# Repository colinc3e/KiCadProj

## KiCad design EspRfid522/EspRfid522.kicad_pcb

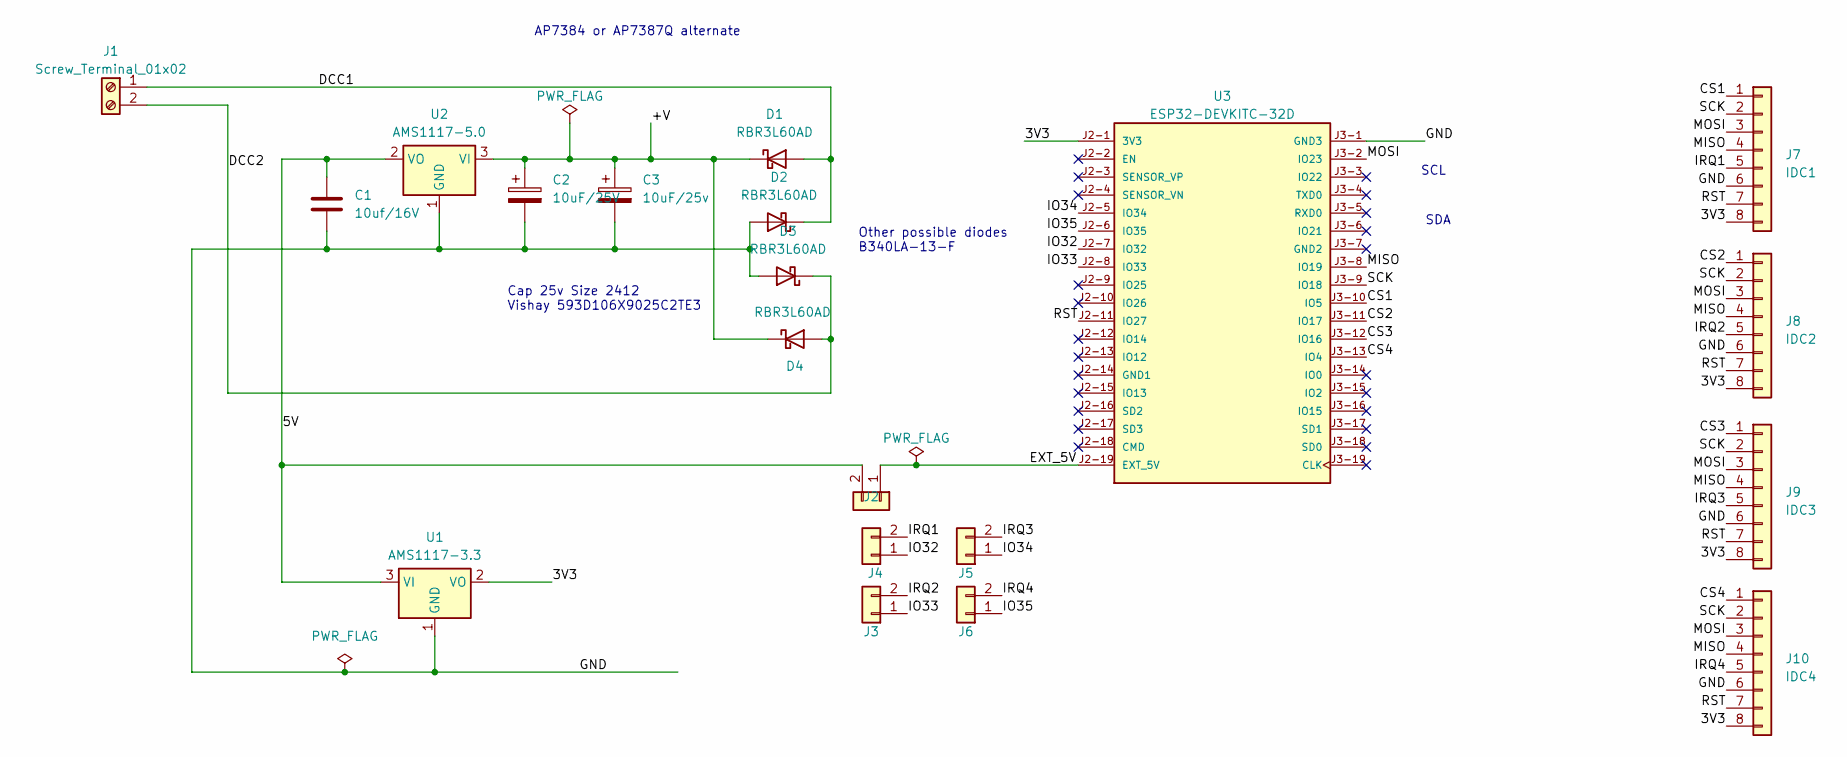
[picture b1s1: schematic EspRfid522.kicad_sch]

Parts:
C1: 10uf/16V; C_1206_3216Metric_Pad1.33x1.80mm_HandSolder
C2: 10uF/25V; CP_EIA-6032-20_AVX-F_Pad2.25x2.35mm_HandSolder
C3: 10uF/25v; CP_EIA-6032-20_AVX-F_Pad2.25x2.35mm_HandSolder
D1, D2, D3, D4: RBR3L60AD; D_SMA_Handsoldering
J1: Screw_Terminal_01x02; TerminalBlock_Phoenix_PT-1,5-2-3.5-H_1x02_P3.50mm_Horizontal
J2, J3, J4, J5, J6: Conn_01x02; PinHeader_1x02_P2.54mm_Vertical
J7: IDC1; IDC-Header_2x04_P2.54mm_Vertical
J8: IDC2; IDC-Header_2x04_P2.54mm_Vertical
J9: IDC3; IDC-Header_2x04_P2.54mm_Vertical
J10: IDC4; IDC-Header_2x04_P2.54mm_Vertical
U1: AMS1117-3.3; SOT-223-3_TabPin2
U2: AMS1117-5.0; SOT-223-3_TabPin2
U3: ESP32-DEVKITC-32D; MODULE_ESP32-DEVKITC-32D; PARTREV V4

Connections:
/3V3: J7.8, J8.8, J9.8, J10.8, U1.2 (VO), U3.J2-1 (3V3)
/5V: C1.1, J4.2, U1.3 (VI), U2.2 (VO)
/+V: C2.1, C3.1, D1.1 (K), D4.1 (K), U2.3 (VI)
/CS1: J7.1, U3.J3-10 (IO5)
/CS2: J8.1, U3.J3-11 (IO17)
/CS3: J9.1, U3.J3-12 (IO16)
/CS4: J10.1, U3.J3-13 (IO4)
/DCC1: D1.2 (A), D2.1 (K), J1.1
/DCC2: D3.1 (K), D4.2 (A), J1.2
/EXT_5V: J4.1, U3.J2-19 (EXT_5V)
/GND: C1.2, C2.2, C3.2, D2.2 (A), D3.2 (A), J7.6, J8.6, J9.6, J10.6, U1.1 (GND), U2.1 (GND), U3.J3-1 (GND3)
/IO32: J2.1, U3.J2-7 (IO32)
/IO33: J3.1, U3.J2-8 (IO33)
/IO34: J5.1, U3.J2-5 (IO34)
/IO35: J6.1, U3.J2-6 (IO35)
/IRQ1: J2.2, J7.5
/IRQ2: J3.2, J8.5
/IRQ3: J5.2, J9.5
/IRQ4: J6.2, J10.5
/MISO: J7.4, J8.4, J9.4, J10.4, U3.J3-8 (IO19)
/MOSI: J7.3, J8.3, J9.3, J10.3, U3.J3-2 (IO23)
/RST: J7.7, J8.7, J9.7, J10.7, U3.J2-11 (IO27)
/SCK: J7.2, J8.2, J9.2, J10.2, U3.J3-9 (IO18)

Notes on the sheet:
SDA
AP7384 or AP7387Q alternate
Other possible diodes B340LA-13-F
SCL
Cap 25v Size 2412 Vishay 593D106X9025C2TE3

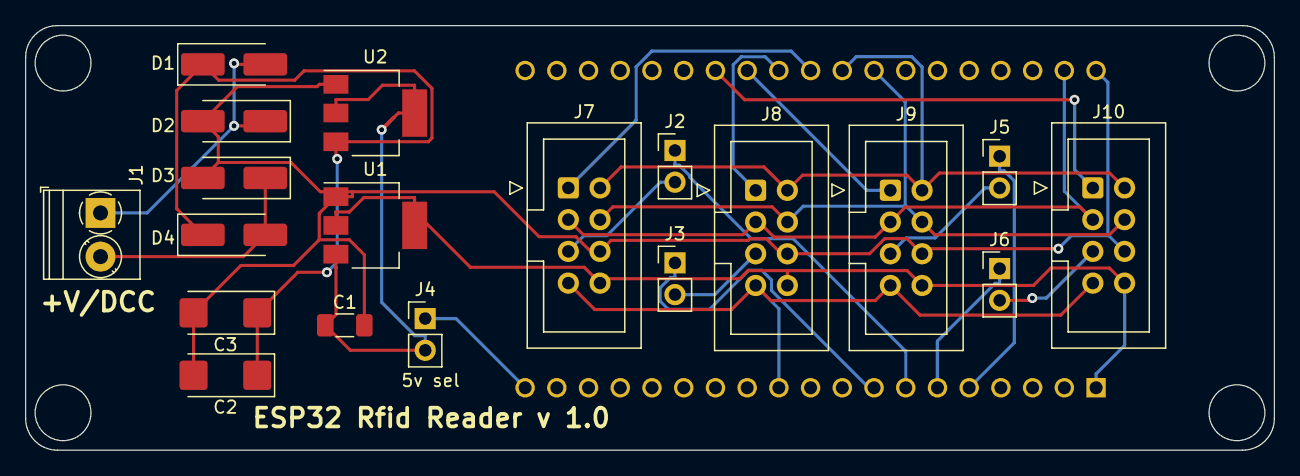
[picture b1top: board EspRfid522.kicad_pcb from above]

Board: 2 copper layers, 100.0 x 34.0 mm, 20 parts (1 on the bottom side), 23 nets.

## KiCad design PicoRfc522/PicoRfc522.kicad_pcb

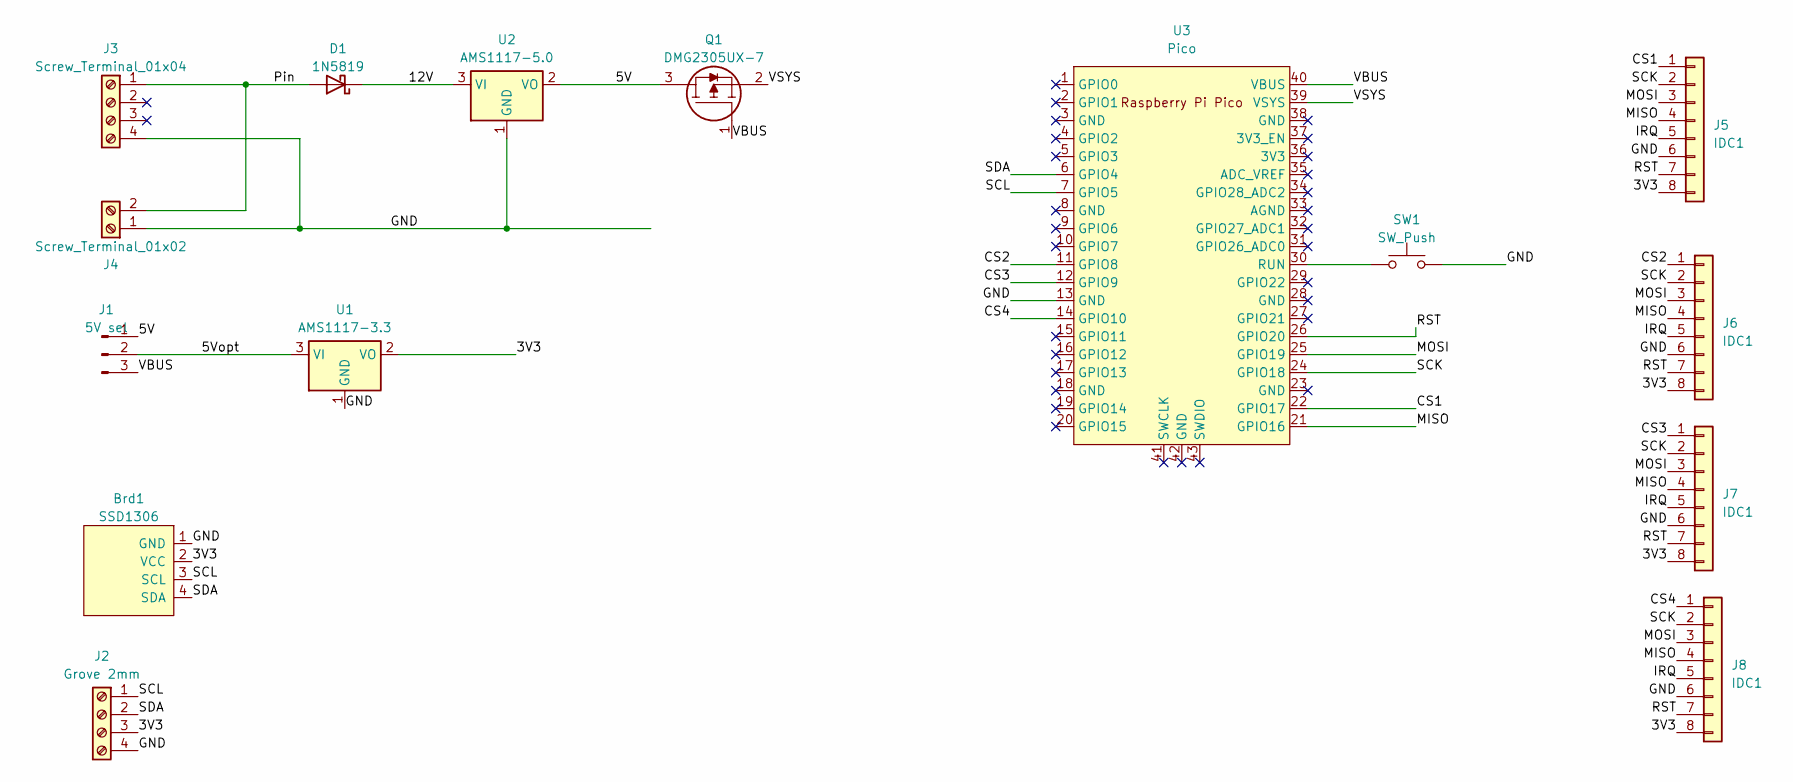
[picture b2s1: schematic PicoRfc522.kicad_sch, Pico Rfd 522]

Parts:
Brd1: SSD1306; 128x64OLED
D1: 1N5819; D_DO-41_SOD81_P10.16mm_Horizontal
J1: 5V sel; PinHeader_1x03_P2.54mm_Vertical
J2: Grove 2mm; HW4-2.0
J3: Screw_Terminal_01x04; TerminalBlock_Phoenix_PT-1,5-4-3.5-H_1x04_P3.50mm_Horizontal
J4: Screw_Terminal_01x02; TerminalBlock_Phoenix_PT-1,5-2-3.5-H_1x02_P3.50mm_Horizontal
J5, J6, J7, J8: IDC1; IDC-Header_2x04_P2.54mm_Vertical
Q1: DMG2305UX-7; SOT96P240X110-3N; Mouser Part Number 621-DMG2305UX-7
SW1: SW_Push; SW_Tactile_SPST_NO_Straight_CK_PTS636Sx25SMTRLFS
U1: AMS1117-3.3; SOT-223-3_TabPin2
U2: AMS1117-5.0; SOT-223-3_TabPin2
U3: Pico; RPi_Pico_SMD_TH

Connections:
/3V3: Brd1.2 (VCC), J2.3, J5.8, J6.8, J7.8, J8.8, U1.2 (VO)
/5V: J1.1, Q1.3, U2.2 (VO)
/5Vopt: J1.2, U1.3 (VI)
/12V: D1.1 (K), U2.3 (VI)
/CS1: J5.1, U3.22 (GPIO17)
/CS2: J6.1, U3.11 (GPIO8)
/CS3: J7.1, U3.12 (GPIO9)
/CS4: J8.1, U3.14 (GPIO10)
/GND: Brd1.1 (GND), J2.4, J3.4, J4.1, J5.6, J6.6, J7.6, J8.6, SW1.1, U1.1 (GND), U2.1 (GND), U3.13 (GND)
/IRQ: J5.5, J6.5, J7.5, J8.5
/MISO: J5.4, J6.4, J7.4, J8.4, U3.21 (GPIO16)
/MOSI: J5.3, J6.3, J7.3, J8.3, U3.25 (GPIO19)
/Pin: D1.2 (A), J3.1, J4.2
/RST: J5.7, J6.7, J7.7, J8.7, U3.26 (GPIO20)
/SCK: J5.2, J6.2, J7.2, J8.2, U3.24 (GPIO18)
/SCL: Brd1.3 (SCL), J2.1, U3.7 (GPIO5)
/SDA: Brd1.4 (SDA), J2.2, U3.6 (GPIO4)
/VBUS: J1.3, Q1.1, U3.40 (VBUS)
/VSYS: Q1.2, U3.39 (VSYS)
unnamed: SW1.2, U3.30 (RUN)

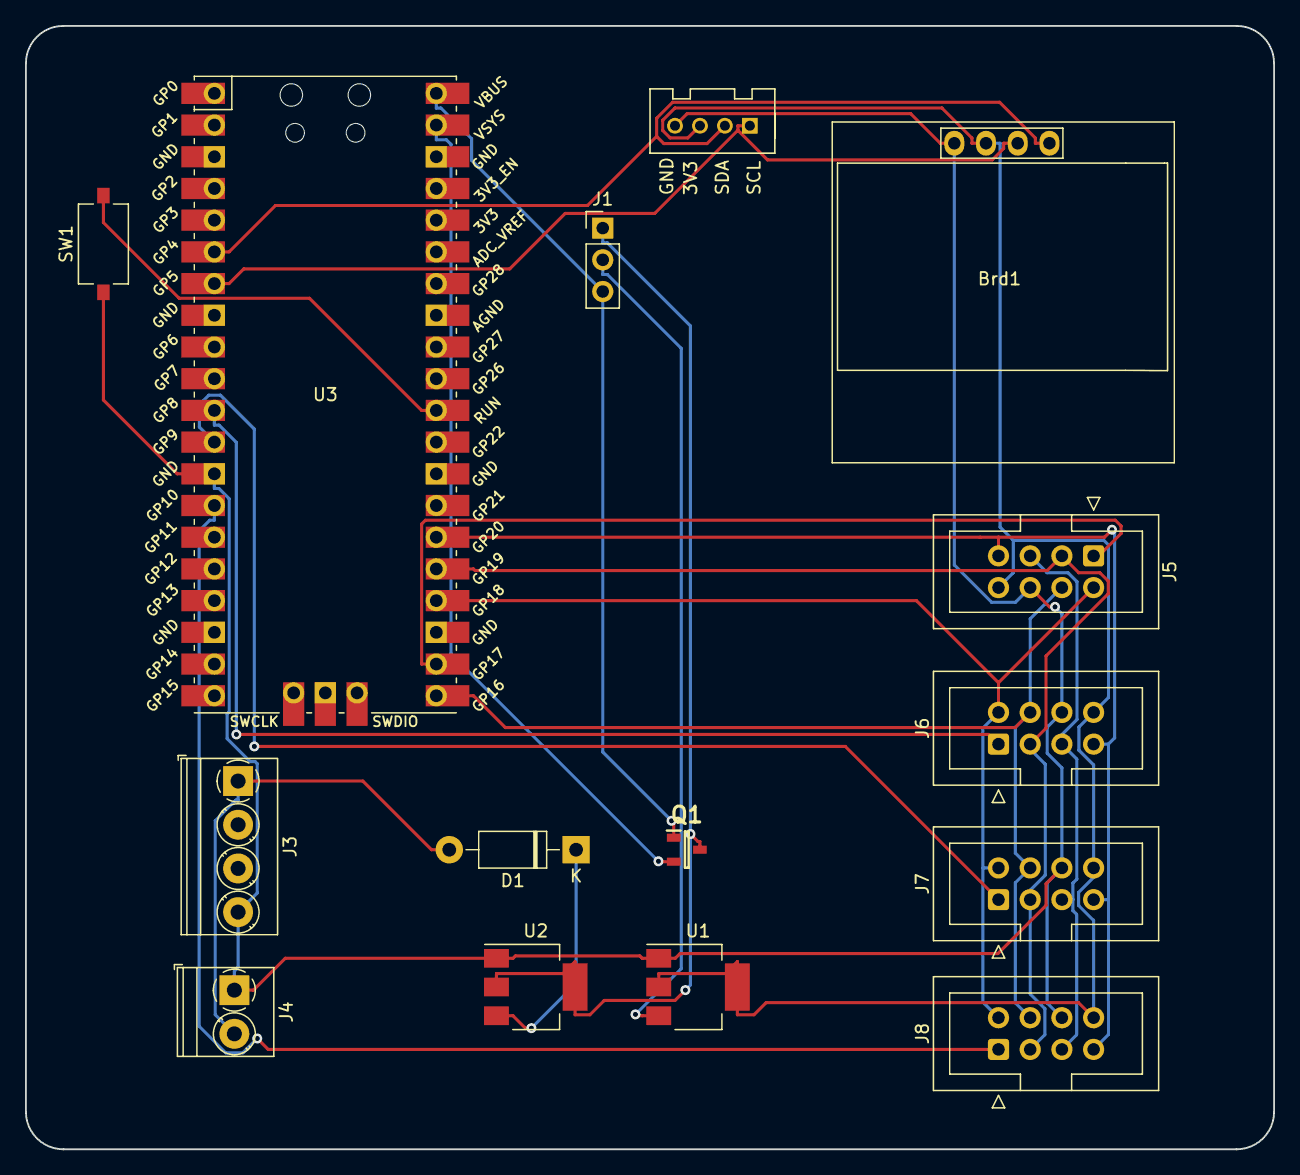
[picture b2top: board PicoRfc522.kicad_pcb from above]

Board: 2 copper layers, 100.0 x 90.0 mm, 15 parts (0 on the bottom side), 20 nets.

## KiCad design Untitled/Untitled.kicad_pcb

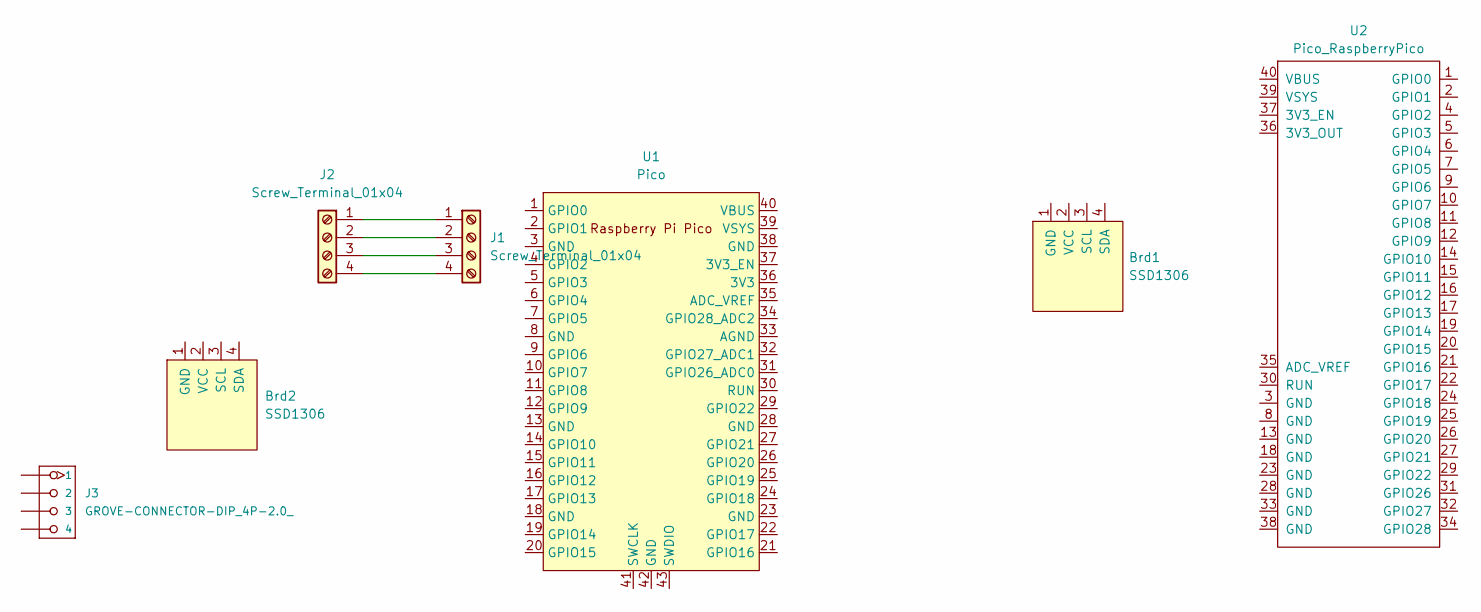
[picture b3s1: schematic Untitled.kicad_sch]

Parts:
Brd1, Brd2: SSD1306; 128x64OLED
J1, J2: Screw_Terminal_01x04; TerminalBlock_Phoenix_PT-1,5-4-3.5-H_1x04_P3.50mm_Horizontal
J3: GROVE-CONNECTOR-DIP_4P-2.0_; HW4-2.0
U1: Pico; RPi_Pico_SMD_TH
U2: Pico_RaspberryPico; RPi_Pico_SMD_TH

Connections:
unnamed: J1.1, J2.1
unnamed: J1.2, J2.2
unnamed: J1.3, J2.3
unnamed: J1.4, J2.4

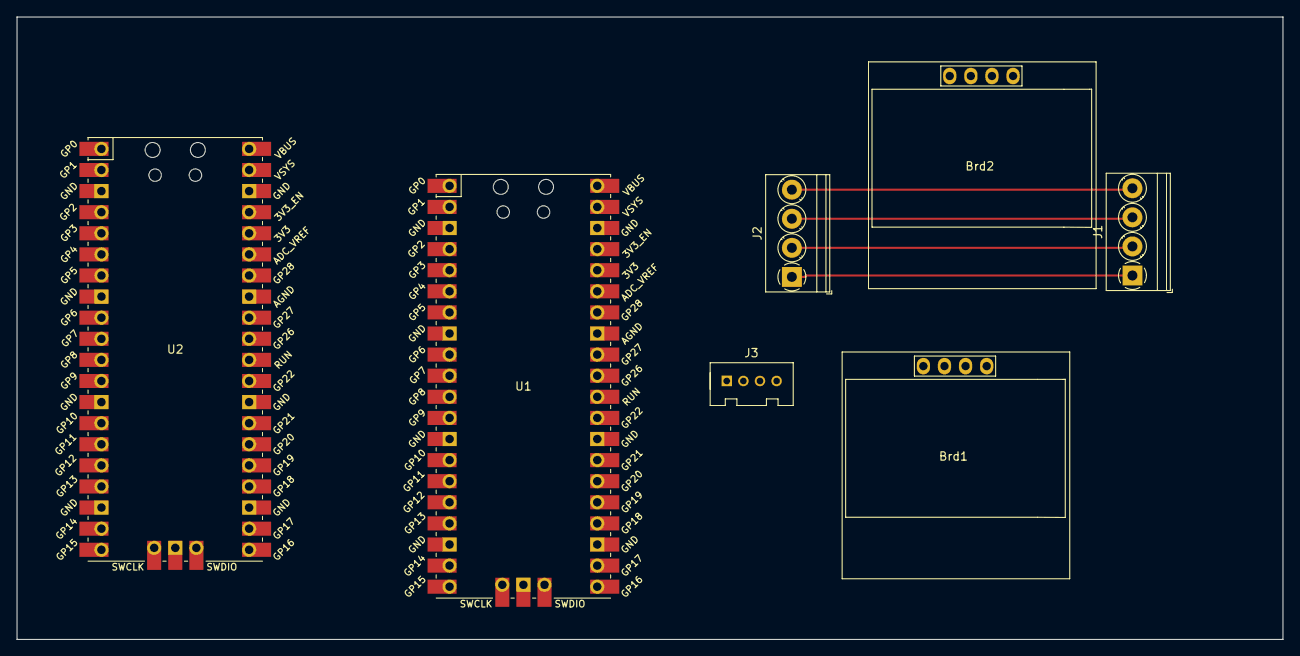
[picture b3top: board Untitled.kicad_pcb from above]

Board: 2 copper layers, 152.4 x 74.9 mm, 7 parts (0 on the bottom side), 4 nets.

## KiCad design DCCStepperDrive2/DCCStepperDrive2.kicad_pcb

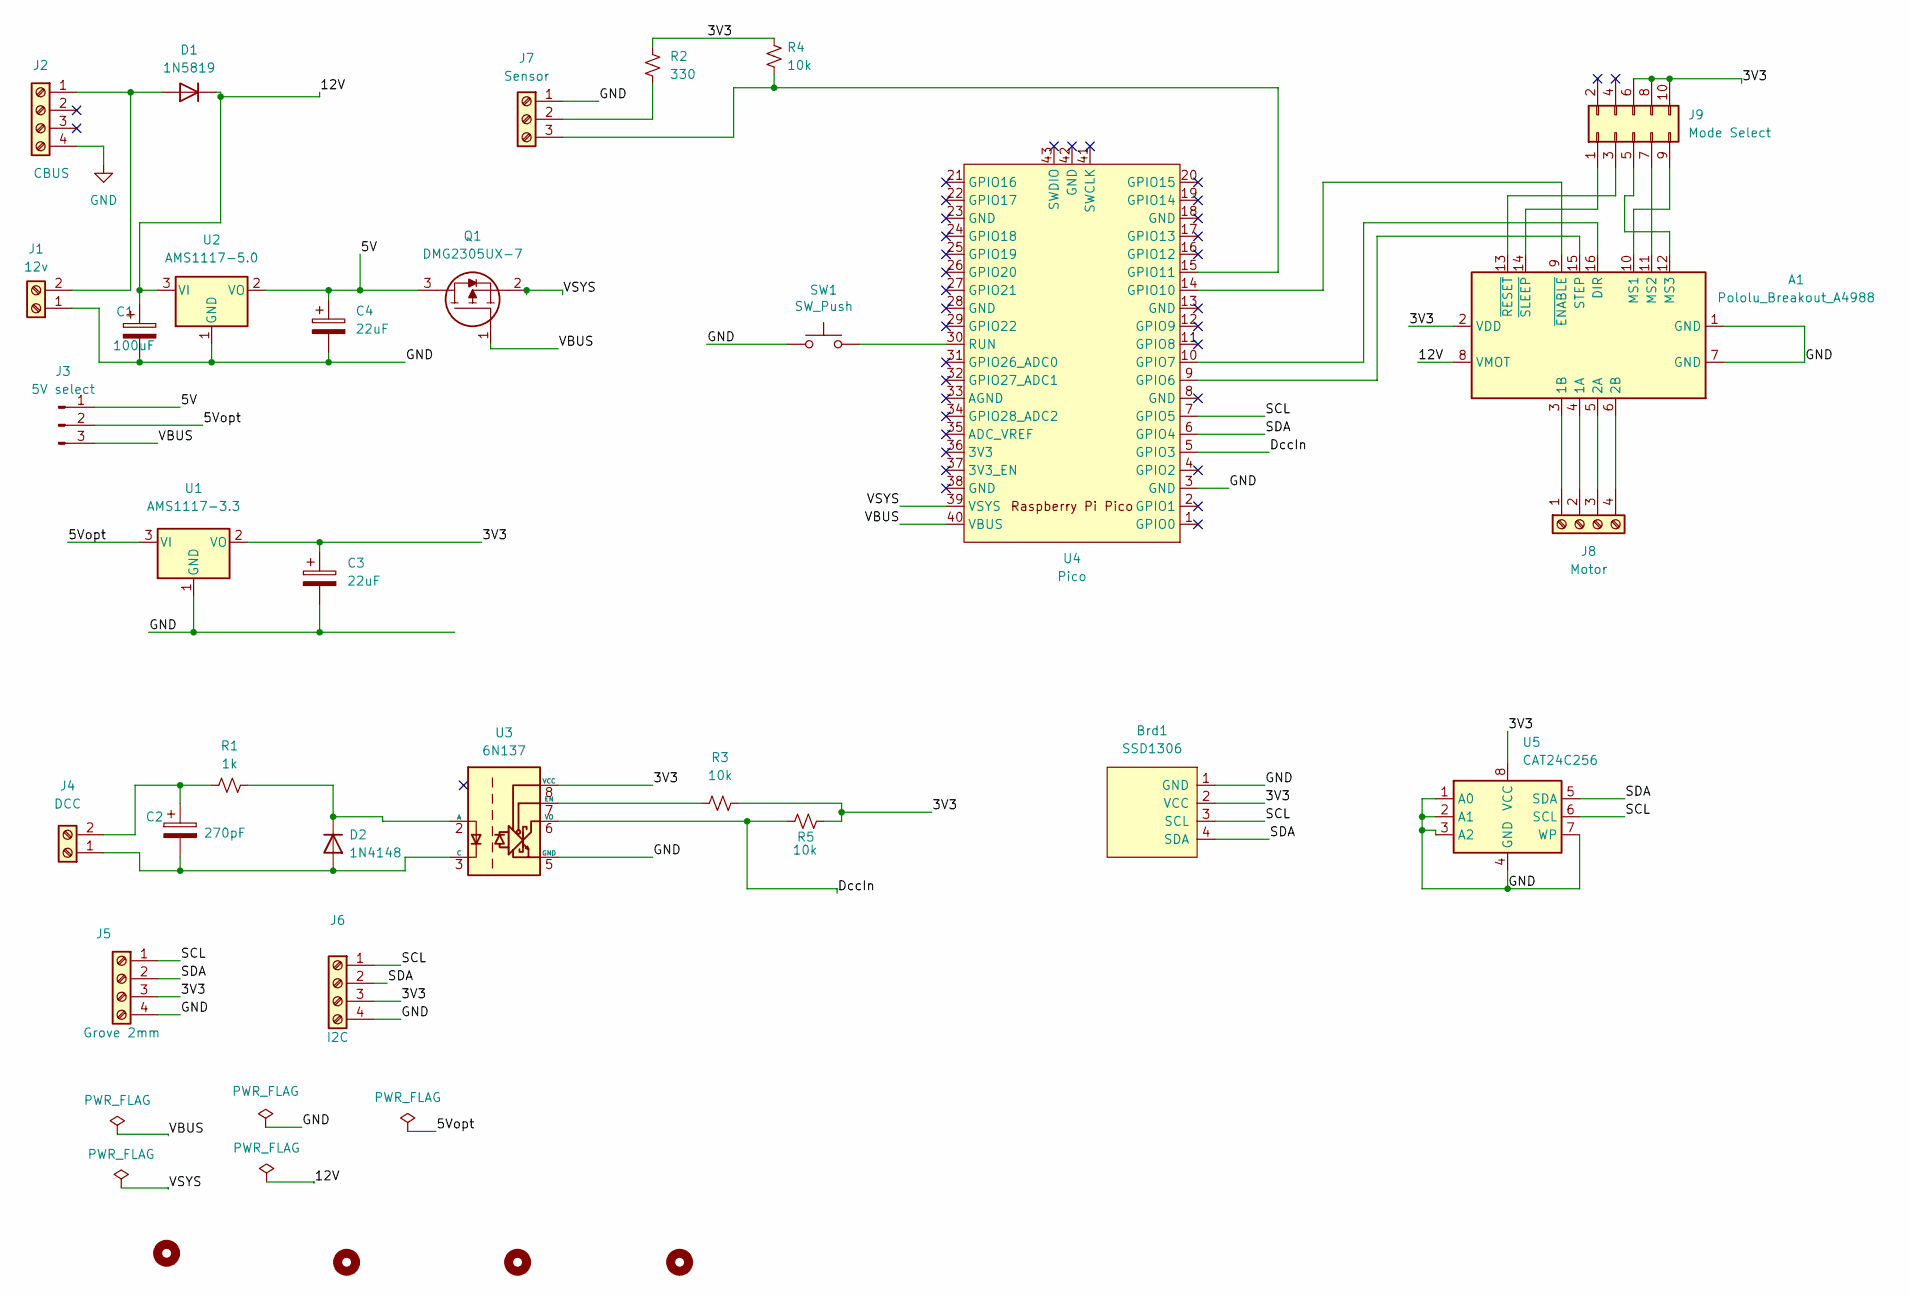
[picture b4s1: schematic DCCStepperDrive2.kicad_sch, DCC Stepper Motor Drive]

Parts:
A1: Pololu_Breakout_A4988; Pololu_Breakout-16_15.2x20.3mm
Brd1: SSD1306; 128x64OLED
C1: 100uF; CP_Radial_D10.0mm_P7.50mm
C2: 270pF; CP_Radial_Tantal_D7.0mm_P5.00mm
C3, C4: 22uF; CP_Radial_Tantal_D7.0mm_P5.00mm
D1: 1N5819; D_DO-41_SOD81_P10.16mm_Horizontal
D2: 1N4148; D_DO-35_SOD27_P7.62mm_Horizontal
H1, H2, H3, H4: MountingHole; MountingHole_3.2mm_M3
J1: 12v; TerminalBlock_Phoenix_PT-1,5-2-3.5-H_1x02_P3.50mm_Horizontal
J2: CBUS; TerminalBlock_Phoenix_PT-1,5-4-3.5-H_1x04_P3.50mm_Horizontal
J3: 5V select; PinHeader_1x03_P2.54mm_Vertical
J4: DCC; TerminalBlock_Phoenix_PT-1,5-2-3.5-H_1x02_P3.50mm_Horizontal
J5: Grove 2mm; HW4-2.0
J6: I2C; HW4-2.0
J7: Sensor; TerminalBlock_Phoenix_PT-1,5-3-3.5-H_1x03_P3.50mm_Horizontal
J8: Motor; TerminalBlock_Phoenix_PT-1,5-4-3.5-H_1x04_P3.50mm_Horizontal
J9: Mode Select; PinHeader_2x05_P2.54mm_Vertical
Q1: DMG2305UX-7; SOT-23-3; Mouser Part Number 621-DMG2305UX-7
R1: 1k; R_1206_3216Metric
R2: 330; R_1206_3216Metric
R3, R4, R5: 10k; R_1206_3216Metric
SW1: SW_Push; SW_Tactile_SPST_NO_Straight_CK_PTS636Sx25SMTRLFS
U1: AMS1117-3.3; SOT-223-3_TabPin2
U2: AMS1117-5.0; SOT-223-3_TabPin2
U3: 6N137; DIP-8_W7.62mm
U4: Pico; RPi_Pico_SMD_TH
U5: CAT24C256; DIP-8_W7.62mm_LongPads

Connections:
/3V3: A1.2 (VDD), Brd1.2 (VCC), C3.1, J5.3, J6.3, J9.6, J9.8, J9.10, R2.2, R3.2, R4.2, R5.2, U1.2 (VO), U3.8 (VCC), U5.8 (VCC)
/5V: C4.1, J3.1, Q1.3, U2.2 (VO)
/5Vopt: J3.2, U1.3 (VI)
/12V: A1.8 (VMOT), C1.1, D1.1 (K), U2.3 (VI)
/DccIn: R5.1, U3.6 (VO), U4.5 (GPIO3)
/SCL: Brd1.3 (SCL), J5.1, J6.1, U4.7 (GPIO5), U5.6 (SCL)
/SDA: Brd1.4 (SDA), J5.2, J6.2, U4.6 (GPIO4), U5.5 (SDA)
/VBUS: J3.3, Q1.1, U4.40 (VBUS)
/VSYS: Q1.2, U4.39 (VSYS)
GND: A1.1 (GND), A1.7 (GND), Brd1.1 (GND), C1.2, C3.2, C4.2, J1.1, J2.4, J5.4, J6.4, J7.1, SW1.1, U1.1 (GND), U2.1 (GND), U3.5 (GND), U4.3 (GND), U5.1 (A0), U5.2 (A1), U5.3 (A2), U5.4 (GND), U5.7 (WP)
unnamed: A1.4 (1A), J8.2
unnamed: A1.3 (1B), J8.1
unnamed: A1.5 (2A), J8.3
unnamed: A1.6 (2B), J8.4
unnamed: A1.16 (DIR), U4.10 (GPIO7)
unnamed: A1.10 (MS1), J9.9
unnamed: A1.11 (MS2), J9.7
unnamed: A1.12 (MS3), J9.5
unnamed: A1.15 (STEP), U4.9 (GPIO6)
unnamed: A1.9 (~ENABLE), U4.14 (GPIO10)
unnamed: A1.13 (~RESET), J9.3
unnamed: A1.14 (~SLEEP), J9.1
unnamed: D1.2 (A), J1.2, J2.1
unnamed: C2.2, D2.2 (A), J4.1, U3.3 (C)
unnamed: D2.1 (K), R1.2, U3.2 (A)
unnamed: C2.1, J4.2, R1.1
unnamed: J7.2, R2.1
unnamed: J7.3, R4.1, U4.15 (GPIO11)
unnamed: R3.1, U3.7 (EN)
unnamed: SW1.2, U4.30 (RUN)

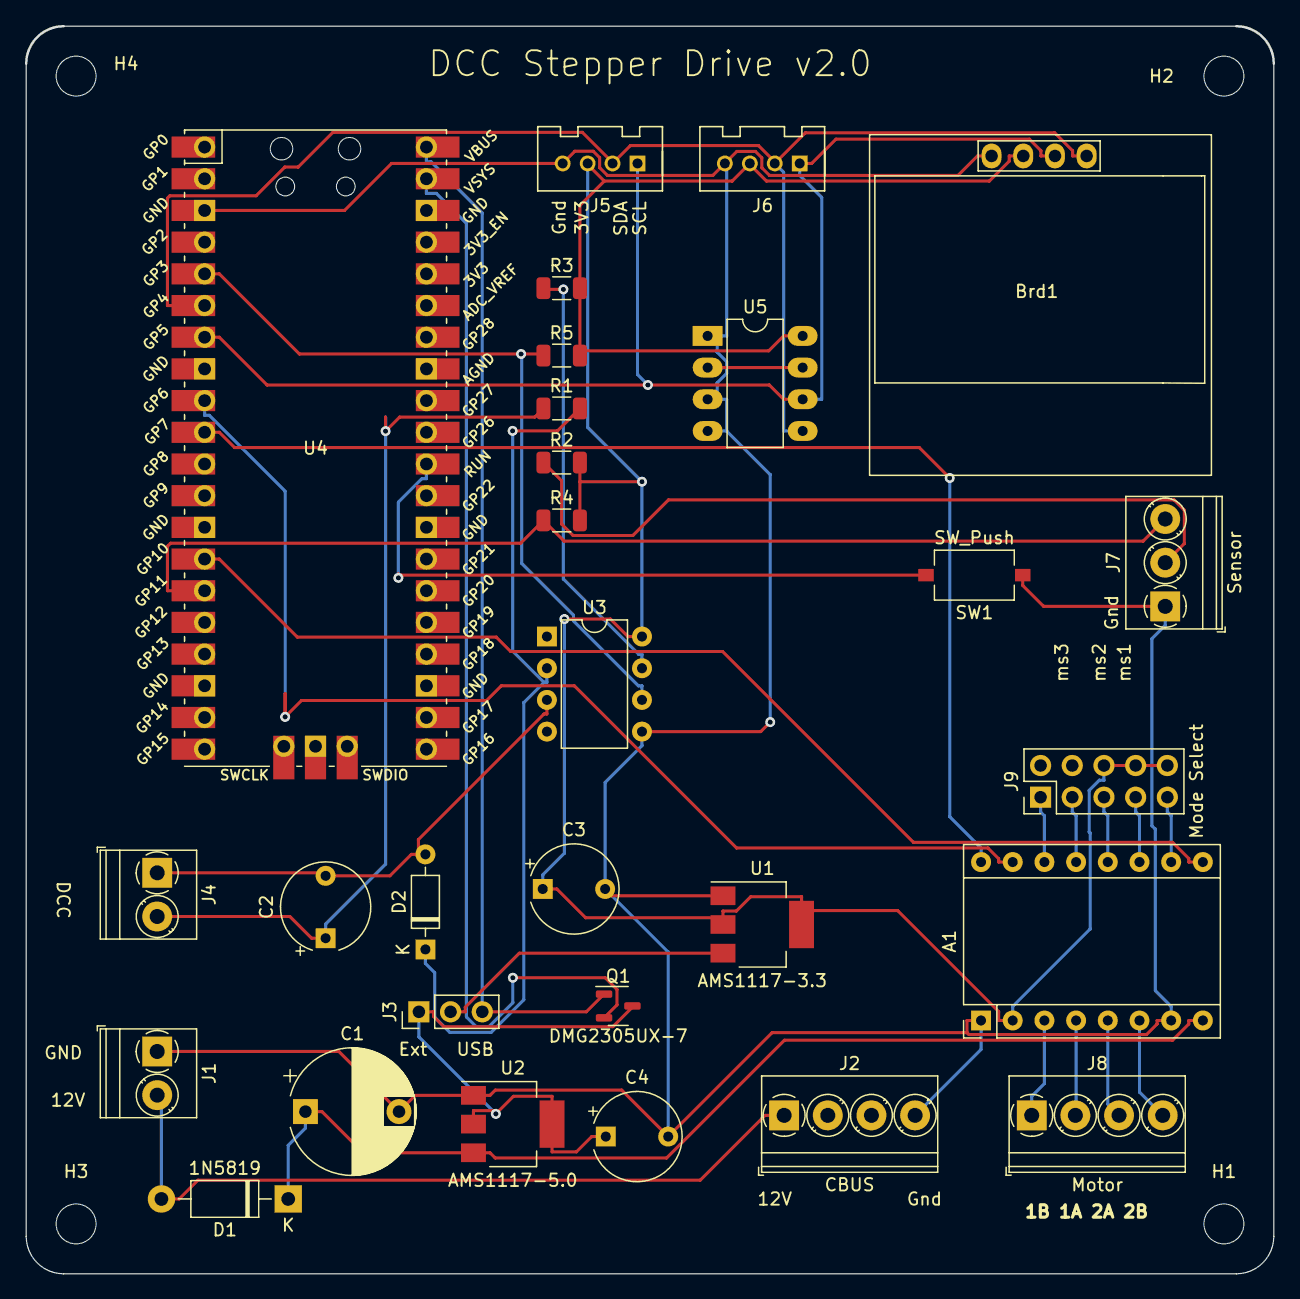
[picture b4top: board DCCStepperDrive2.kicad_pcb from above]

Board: 2 copper layers, 100.0 x 100.0 mm, 33 parts (0 on the bottom side), 30 nets.

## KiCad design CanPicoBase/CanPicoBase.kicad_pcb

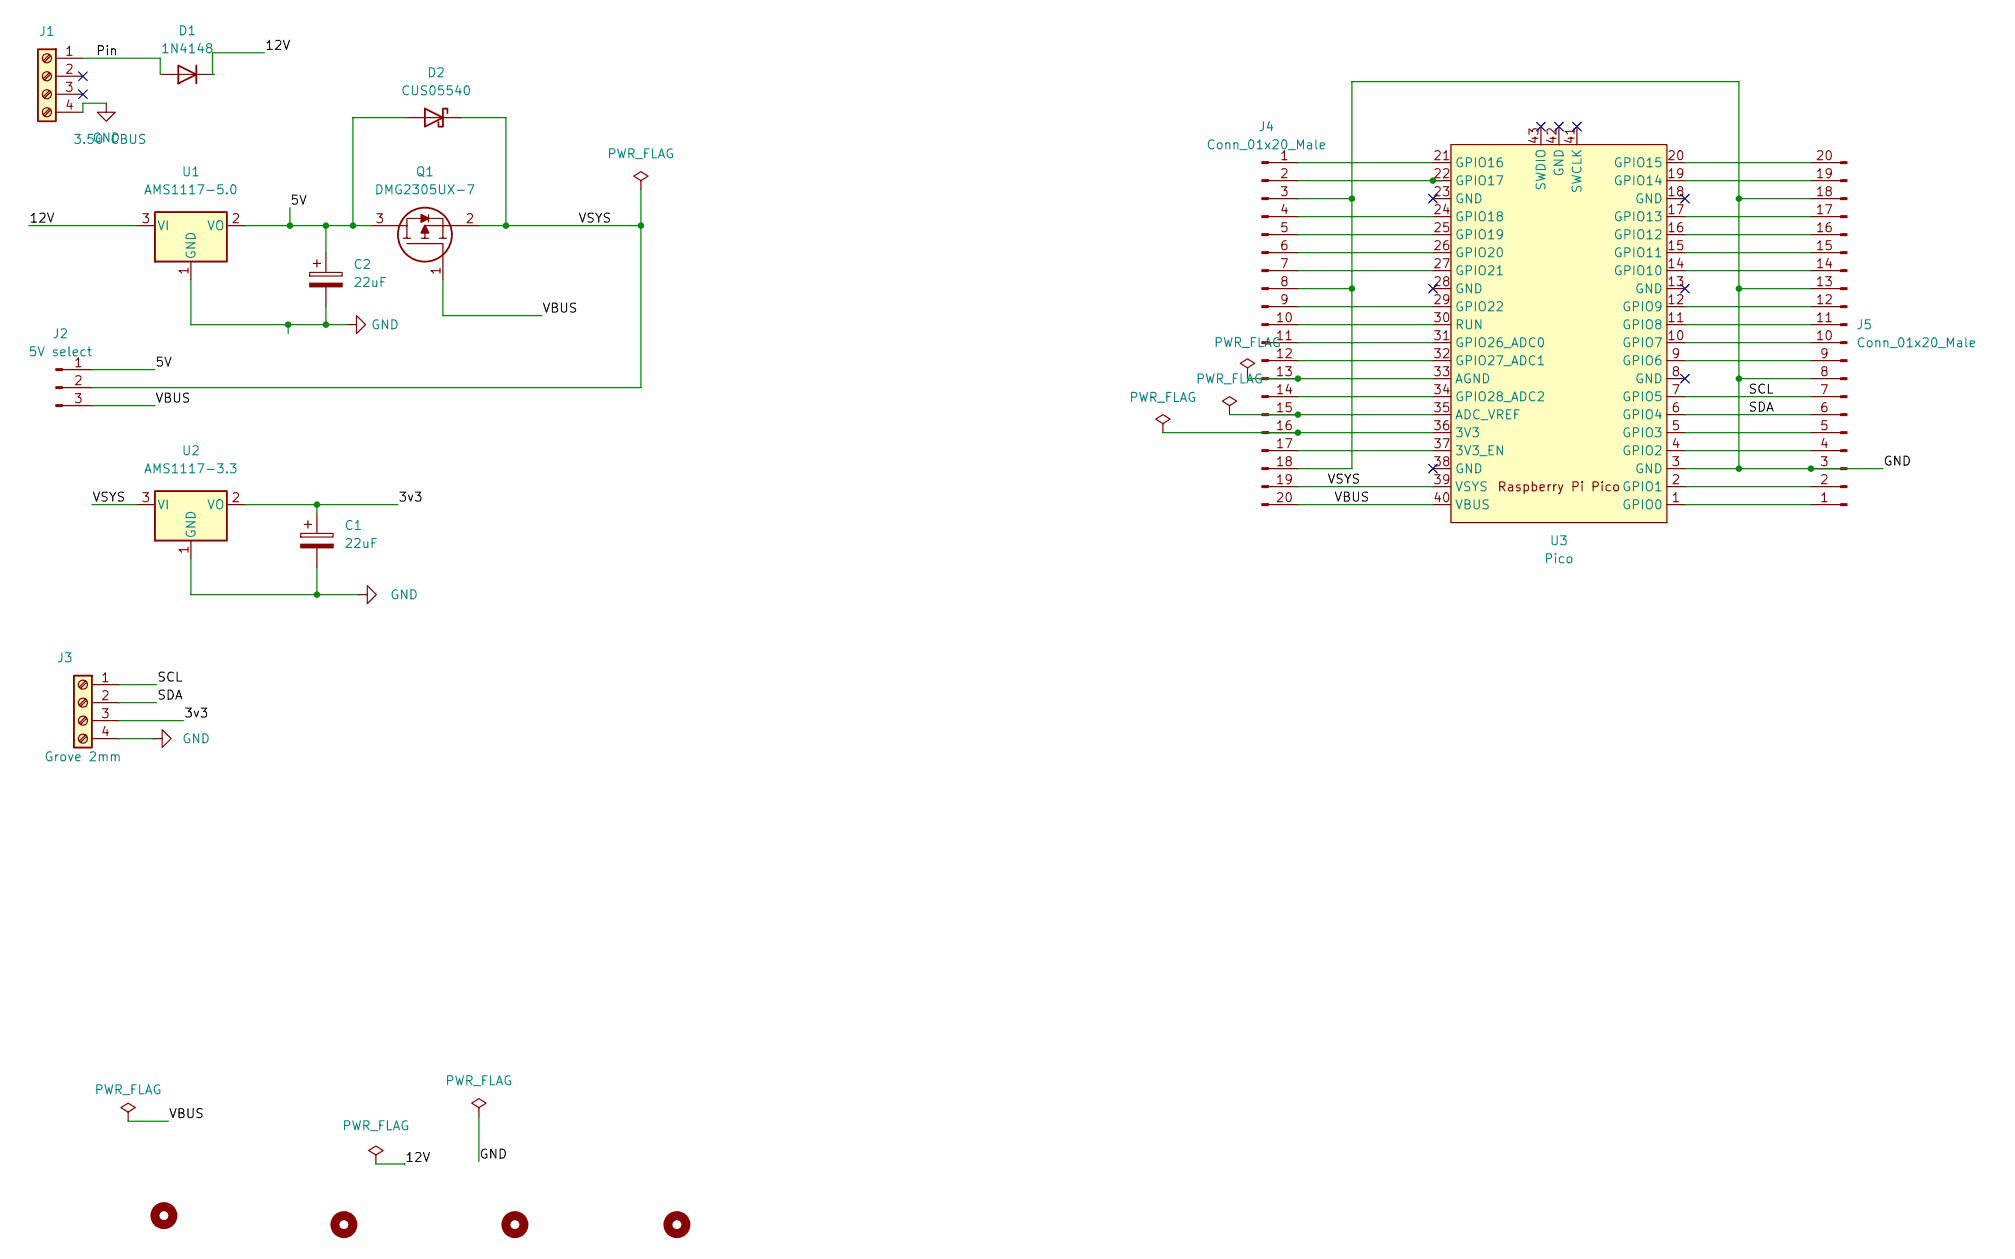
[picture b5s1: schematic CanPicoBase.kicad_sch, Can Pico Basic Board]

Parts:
C1, C2: 22uF; CP_Radial_Tantal_D7.0mm_P5.00mm
D1: 1N4148; D_DO-35_SOD27_P7.62mm_Horizontal
D2: CUS05540; D_SOD-123
H1, H2, H3, H4: MountingHole; MountingHole_3.2mm_M3
J1: 3.50 CBUS; TerminalBlock_Phoenix_PT-1,5-4-3.5-H_1x04_P3.50mm_Horizontal
J2: 5V select; PinHeader_1x03_P2.54mm_Vertical
J3: Grove 2mm; HW4-2.0
J4, J5: Conn_01x20_Male; PinSocket_1x20_P2.54mm_Vertical
Q1: DMG2305UX-7; SOT-23; Mouser Part Number 621-DMG2305UX-7
U1: AMS1117-5.0; SOT-223-3_TabPin2
U2: AMS1117-3.3; SOT-223-3_TabPin2
U3: Pico; RP2040Pico

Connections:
/3v3: C1.1, J3.3, U2.2 (VO)
/5V: C2.1, D2.2 (A), J2.1, Q1.3, U1.2 (VO)
/12V: D1.1 (K), U1.3 (VI)
/SCL: J3.1, J5.7, U3.7 (GPIO5)
/SDA: J3.2, J5.6, U3.6 (GPIO4)
/VBUS: J2.3, J4.20, Q1.1, U3.40 (VBUS)
/VSYS: D2.1 (K), J2.2, J4.19, Q1.2, U2.3 (VI), U3.39 (VSYS)
GND: C1.2, C2.2, J1.4, J3.4, J4.3, J4.8, J4.18, J5.3, J5.8, J5.13, J5.18, U1.1 (GND), U2.1 (GND), U3.3 (GND)
unnamed: D1.2 (A), J1.1
unnamed: J4.1, U3.21 (GPIO16)
unnamed: J4.2, U3.22 (GPIO17)
unnamed: J4.4, U3.24 (GPIO18)
unnamed: J4.5, U3.25 (GPIO19)
unnamed: J4.6, U3.26 (GPIO20)
unnamed: J4.7, U3.27 (GPIO21)
unnamed: J4.9, U3.29 (GPIO22)
unnamed: J4.10, U3.30 (RUN)
unnamed: J4.11, U3.31 (GPIO26_ADC0)
unnamed: J4.12, U3.32 (GPIO27_ADC1)
unnamed: J4.13, U3.33 (AGND)
unnamed: J4.14, U3.34 (GPIO28_ADC2)
unnamed: J4.15, U3.35 (ADC_VREF)
unnamed: J4.16, U3.36 (3V3)
unnamed: J4.17, U3.37 (3V3_EN)
unnamed: J5.1, U3.1 (GPIO0)
unnamed: J5.2, U3.2 (GPIO1)
unnamed: J5.4, U3.4 (GPIO2)
unnamed: J5.5, U3.5 (GPIO3)
unnamed: J5.9, U3.9 (GPIO6)
unnamed: J5.10, U3.10 (GPIO7)
unnamed: J5.11, U3.11 (GPIO8)
unnamed: J5.12, U3.12 (GPIO9)
unnamed: J5.14, U3.14 (GPIO10)
unnamed: J5.15, U3.15 (GPIO11)
unnamed: J5.16, U3.16 (GPIO12)
unnamed: J5.17, U3.17 (GPIO13)
unnamed: J5.19, U3.19 (GPIO14)
unnamed: J5.20, U3.20 (GPIO15)

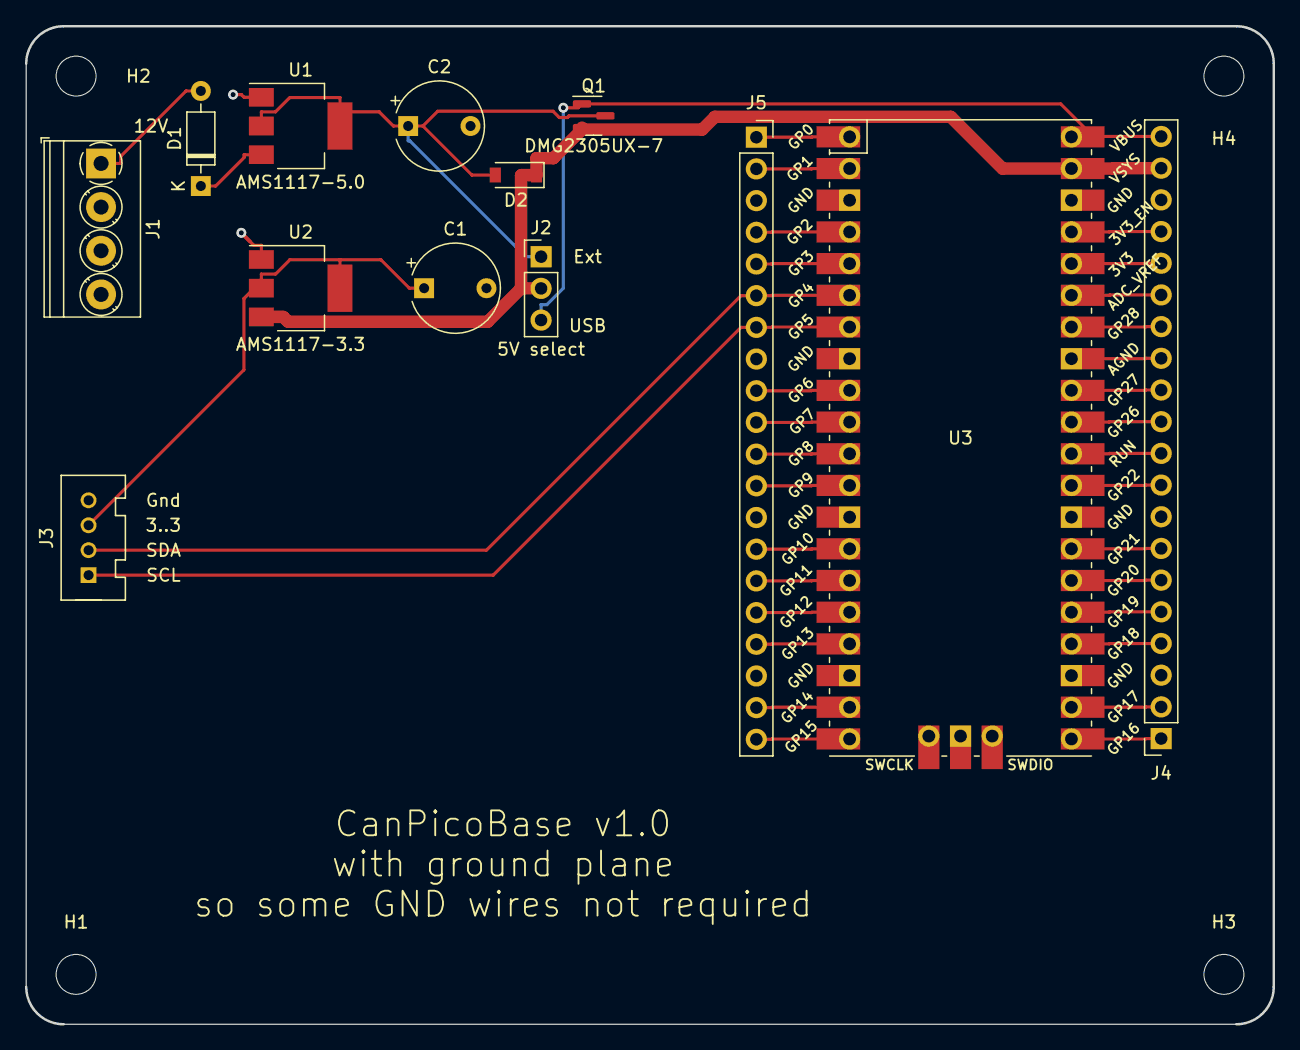
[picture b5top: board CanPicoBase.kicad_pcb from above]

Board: 2 copper layers, 100.0 x 80.0 mm, 17 parts (0 on the bottom side), 38 nets.
